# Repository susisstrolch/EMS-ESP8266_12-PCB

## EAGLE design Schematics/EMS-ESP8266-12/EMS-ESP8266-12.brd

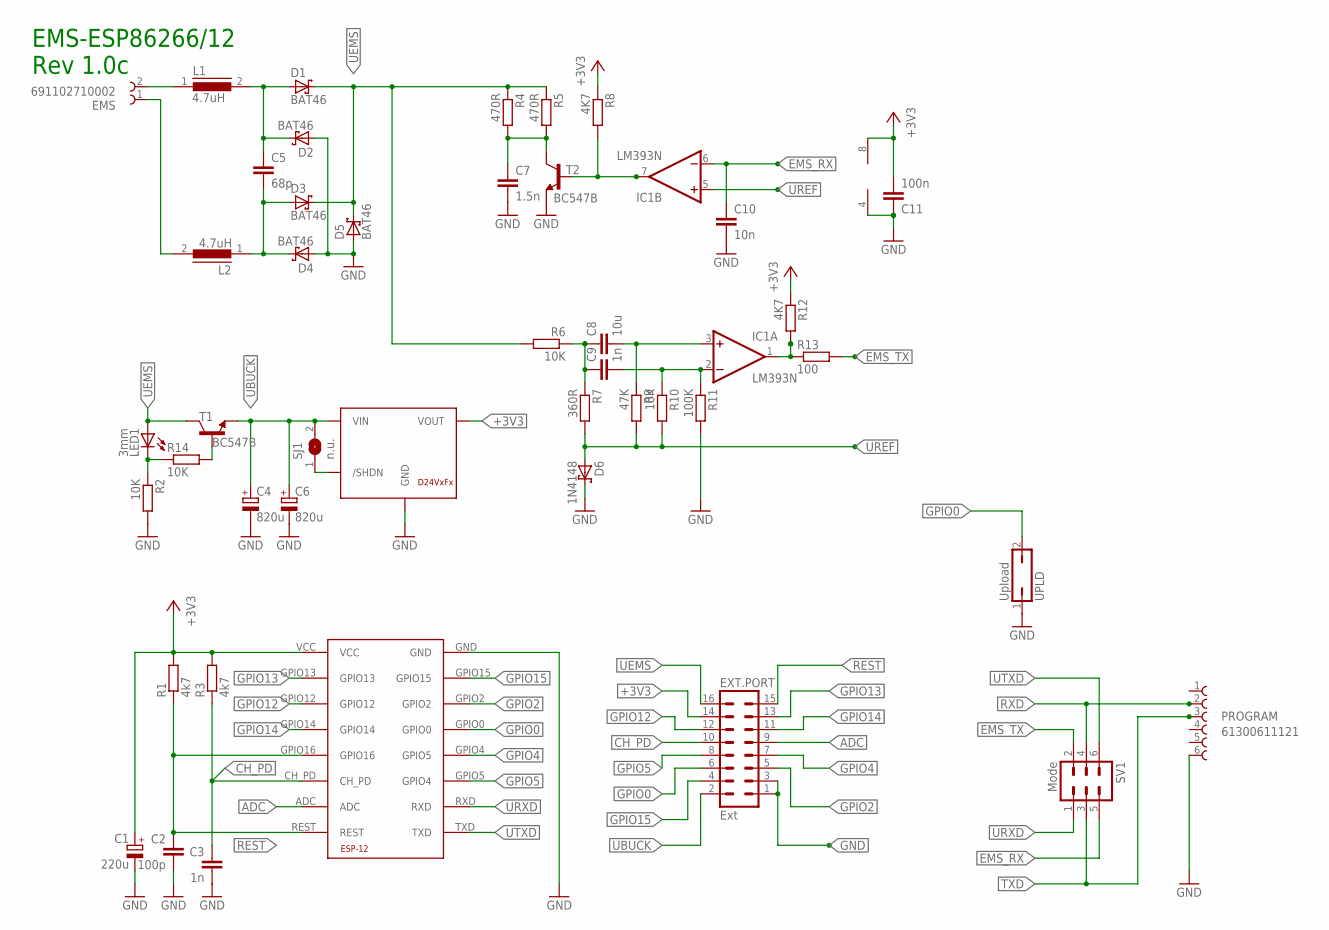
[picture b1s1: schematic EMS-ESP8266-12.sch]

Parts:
C1: 220u; UD-6,3X5,8_NICHICON
C2: 100p; C2.5-2
C3, C9: 1n; C2.5-2
C4, C6: 820u; UD-10X10_NICHICON
C5: 68p; C025-050X050
C7: 1.5n; C2.5-2
C8: 10u; C5B11
C10: 10n; C2.5-2
C11: 100n; C2.5-2
D1, D2, D3, D4, D5: BAT46; DO35-7
D6: 1N4148; DO35-7
EMS: 691102710002
ESP1: ESP-12ESP-12; ESP-12
EXT.PORT: Ext; MA08-2
IC1: LM393N; DIL08
L1, L2: 4.7uH; MICC12
LED1: 3mm; LED3MM
MOD1: D24V3F3; D24VXFX
PROGRAM: 61300611121
R1, R3: 4k7; 0204/7
R2, R6, R10, R14: 10K; 0204/7
R4, R5: 470R; 0204/7
R7: 360R; 0204/7
R8, R12: 4K7; 0204/7
R9: 47K; 0204/7
R11: 100K; 0204/7
R13: 100; 0204/7
SJ1: n.u.; SJ
SV1: Mode; MA03-2
T1, T2: BC547B; TO92
UPLD: Upload; JP1

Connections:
+3V3: C1.+, C11.2, ESP1.VCC, EXT.PORT.14, IC1.8 (V+), MOD1.VOUT, R1.2, R3.2, R8.1, R12.1
ADC: ESP1.ADC, EXT.PORT.9
CH_PD: C3.1, ESP1.CH_PD, EXT.PORT.10, R3.1
EMS_RX: C10.1, IC1.6 (-IN), SV1.5
EMS_TX: R13.2, SV1.2
GND: C1.-, C2.2, C3.2, C4.-, C6.-, C7.2, C10.2, C11.1, D2.A, D4.A, D5.A, D6.C, ESP1.GND, EXT.PORT.1, EXT.PORT.3, IC1.4 (V-), MOD1.GND, PROGRAM.6, R2.2, R11.2, T2.1 (E), UPLD.1
GPIO0: ESP1.GPIO0, EXT.PORT.6, UPLD.2
GPIO2: ESP1.GPIO2, EXT.PORT.5
GPIO4: ESP1.GPIO4 (GPIO5), EXT.PORT.7
GPIO5: ESP1.GPIO5 (GPIO4), EXT.PORT.8
GPIO12: ESP1.GPIO12, EXT.PORT.12
GPIO13: ESP1.GPIO13, EXT.PORT.13
GPIO14: ESP1.GPIO14, EXT.PORT.11
GPIO15: ESP1.GPIO15, EXT.PORT.4
unnamed: C5.1, D1.A, D2.C, L1.2
unnamed: C5.2, D3.A, D4.C, L2.1
unnamed: MOD1./SHDN, SJ1.1
unnamed: EMS.2, L1.1
unnamed: IC1.1 (OUT), R12.2, R13.1
unnamed: C7.1, R4.2, R5.2, T2.3 (C)
unnamed: C8.1, C9.1, R6.1, R7.1
unnamed: EMS.1, L2.2
unnamed: C8.2, IC1.3 (+IN), R9.1
unnamed: R14.2, T1.2 (B)
unnamed: C9.2, IC1.2 (-IN), R10.1, R11.1
unnamed: IC1.7 (OUT), R8.2, T2.2 (B)
unnamed: LED1.K (C), R2.1, R14.1
REST: C2.1, ESP1.GPIO16, ESP1.REST, EXT.PORT.15, R1.1
RXD: PROGRAM.2, SV1.4
TXD: PROGRAM.3, SV1.3
UBUCK: C4.+, C6.+, EXT.PORT.2, MOD1.VIN, SJ1.2, T1.1 (E)
UEMS: D1.C, D3.C, D5.C, EXT.PORT.16, LED1.A, R4.1, R5.1, R6.2, T1.3 (C)
UREF: D6.A, IC1.5 (+IN), R7.2, R9.2, R10.2
URXD: ESP1.RXD, SV1.1
UTXD: ESP1.TXD, SV1.6

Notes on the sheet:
EMS-ESP86266/12 Rev 1.0c

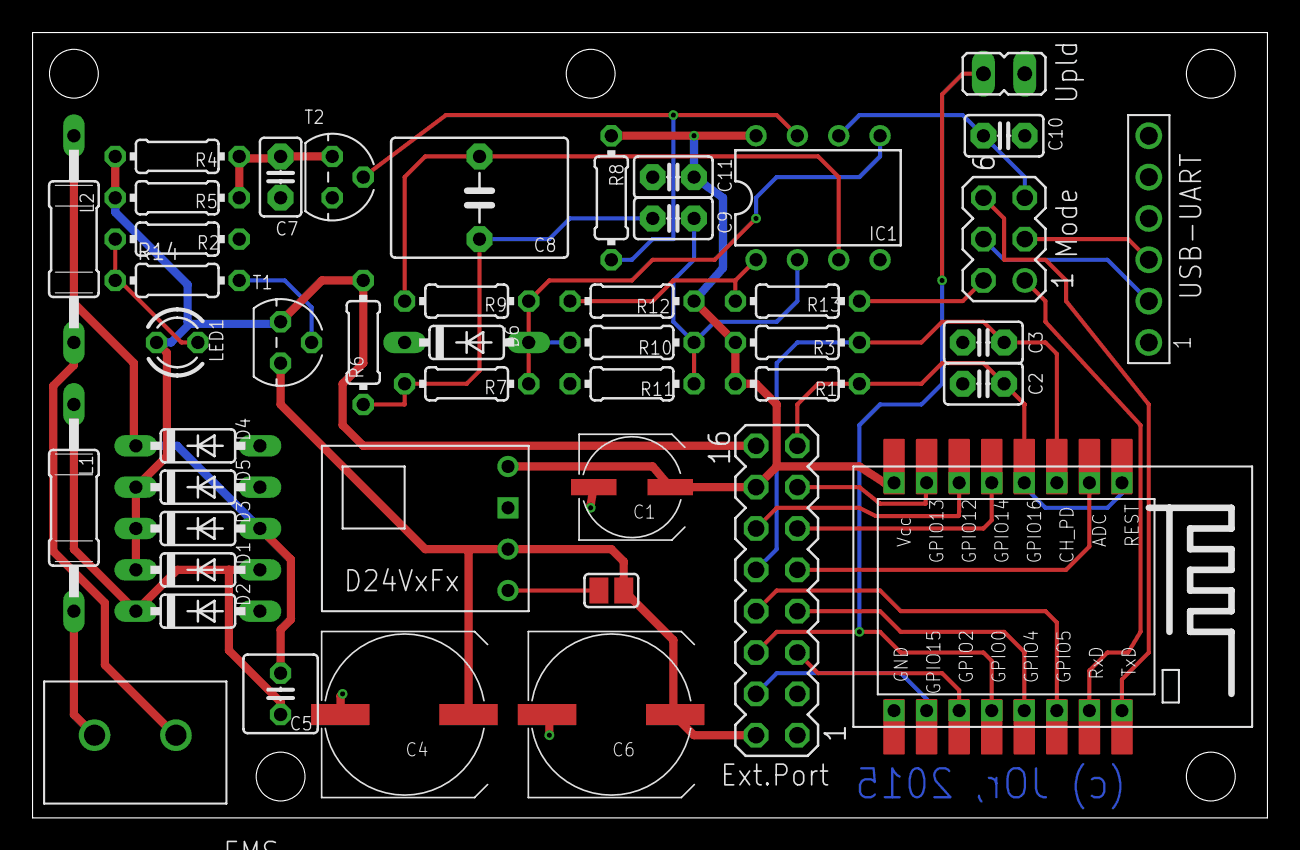
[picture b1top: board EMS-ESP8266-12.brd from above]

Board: 2 copper layers, 75.9 x 48.2 mm, 45 parts (0 on the bottom side), 35 nets.

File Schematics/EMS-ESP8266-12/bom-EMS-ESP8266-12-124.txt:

Partlist exported from /home/jorschiedt/Development/Heizung/EMS-ESP12/Schematics/EMS-ESP8266-12/EMS-ESP8266-12.sch at 2/8/15 2:24 PM

Part     Value        Device               Package             Description                                                          
C1       220u         CPOL-EUUD-6,3X8,8    UD-6,3X5,8_NICHICON POLARIZED CAPACITOR, European symbol                           
C2       100p         C2.5/2               C2.5-2              CAPACITOR
C3       1n           C2.5/2               C2.5-2              CAPACITOR
C4       820u         CPOL-EUUD-10X10      UD-10X10_NICHICON   POLARIZED CAPACITOR, European symbol                           
C5       68p          C-EU025-050X050      C025-050X050        CAPACITOR, European symbol                                      
C6       820u         CPOL-EUUD-10X10      UD-10X10_NICHICON   POLARIZED CAPACITOR, European symbol                          
C7       1.5n         C2.5/2               C2.5-2              CAPACITOR
C8       10u          C5/11                C5B11               CAPACITOR                                                    
C9       1n           C2.5/2               C2.5-2              CAPACITOR                                                   
C10      10n          C2.5/2               C2.5-2              CAPACITOR
C11      100n         C2.5/2               C2.5-2              CAPACITOR
D1       BAT46        SCHOTTKY-DIODEDO35-7 DO35-7              Schottky Diode                                              
D2       BAT46        SCHOTTKY-DIODEDO35-7 DO35-7              Schottky Diode                                              
D3       BAT46        SCHOTTKY-DIODEDO35-7 DO35-7              Schottky Diode                                              
D4       BAT46        SCHOTTKY-DIODEDO35-7 DO35-7              Schottky Diode                                              
D5       BAT46        SCHOTTKY-DIODEDO35-7 DO35-7              Schottky Diode                                              
D6       1N4148       SCHOTTKY-DIODEDO35-7 DO35-7              Schottky Diode                                              
EMS      691102710002 691102710002         691102710002        WR-TBL Serie 102 - 5.0mm Horizontal Entry Modular with Press
ESP1     ESP-12ESP-12 ESP-12ESP-12         ESP-12              low cost Wifi to Serial Module
EXT.PORT Ext          MA08-2               MA08-2              PIN HEADER                                                  
IC1      LM393N       LM393N               DIL08               COMPARATOR
L1       4.7uH        MICC12               MICC12              INDUCTOR                                                    
L2       4.7uH        MICC12               MICC12              INDUCTOR                                                    
LED1     3mm          LED3MM               LED3MM              LED
MOD1     D24V3F3      D24VXFX              D24VXFX             Step-Down Spannungsregler
PROGRAM  61300611121  61300611121          61300611121         WR-PHD 2.54mm Pin Header, 6 Pin =>Code : Con_BTB_PHD_2.54_1_
R1       4k7          R-EU_0204/7          0204/7              RESISTOR, European symbol
R2       10K          R-EU_0204/7          0204/7              RESISTOR, European symbol
R3       4k7          R-EU_0204/7          0204/7              RESISTOR, European symbol
R4       470R         R-EU_0204/7          0204/7              RESISTOR, European symbol
R5       470R         R-EU_0204/7          0204/7              RESISTOR, European symbol
R6       10K          R-EU_0204/7          0204/7              RESISTOR, European symbol
R7       360R         R-EU_0204/7          0204/7              RESISTOR, European symbol
R8       4K7          R-EU_0204/7          0204/7              RESISTOR, European symbol
R9       47K          R-EU_0204/7          0204/7              RESISTOR, European symbol
R10      10K          R-EU_0204/7          0204/7              RESISTOR, European symbol
R11      100K         R-EU_0204/7          0204/7              RESISTOR, European symbol
R12      4K7          R-EU_0204/7          0204/7              RESISTOR, European symbol
R13      100          R-EU_0204/7          0204/7              RESISTOR, European symbol
SJ1      n.u.         SJ                   SJ                  SMD solder JUMPER
SV1      Mode         MA03-2               MA03-2              PIN HEADER                                                 
T1       BC547B       -NPN-TO92-EBC        TO92-EBC            NPN Transistror
T2       BC547B       -NPN-TO92-EBC        TO92-EBC            NPN Transistror
UPLD     Upload       JP1Q                 JP1                 JUMPER

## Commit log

2015-08-05 sweeping...
2016-01-17 EMS-ESP86266/12 Rev 1.0c
    - Basiswiderstand R14 (10k) zur Strombegrenzung
    - Package für T1,T2 in TO92 geändert
2016-03-03 update...

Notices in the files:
parts and their libraries:
EagleLibrary_Wuerth_Elektronik_eiCan_Ter: Copyright: WÃÂÃÂÃÂÃÂ¼rth Elektronik
EagleLibrary_Wuerth_Elektronik_eiCan_Ter: Copyright: Würth Elektronik
